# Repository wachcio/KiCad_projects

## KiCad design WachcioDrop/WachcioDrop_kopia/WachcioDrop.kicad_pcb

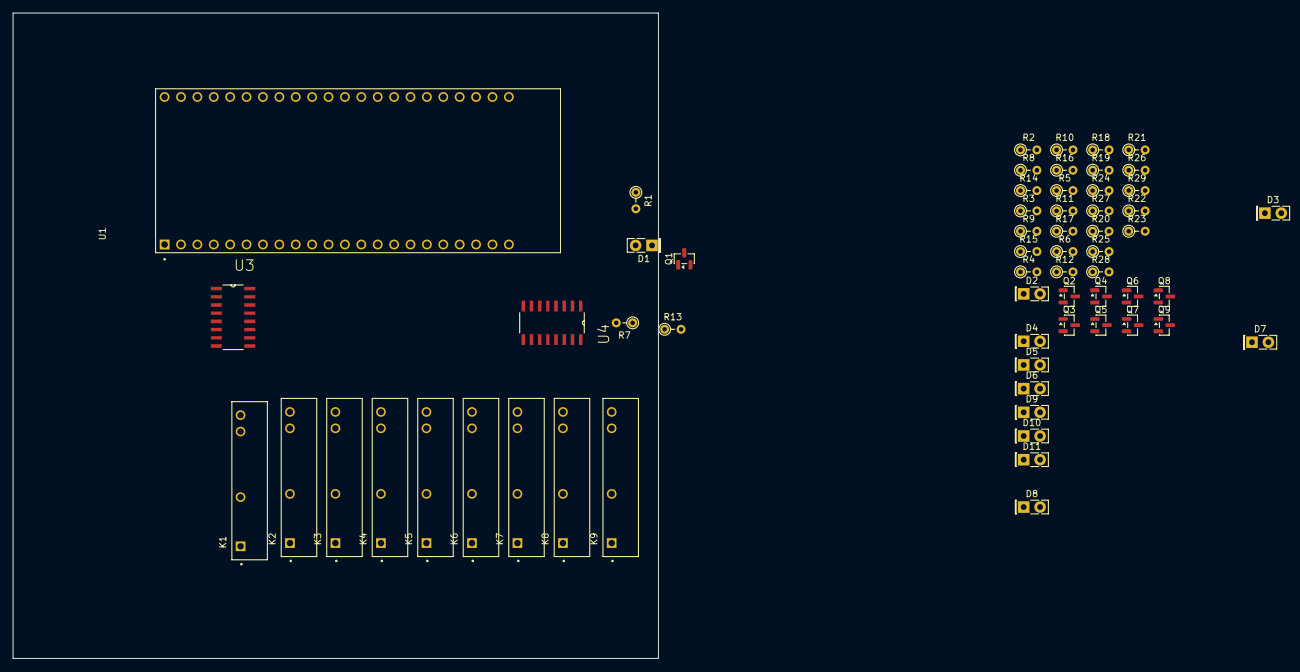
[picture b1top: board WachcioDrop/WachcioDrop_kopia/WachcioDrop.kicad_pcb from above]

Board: 2 copper layers, 100.0 x 100.0 mm, 61 parts (0 on the bottom side), 47 nets, no tracks yet.

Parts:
D1, D2, D3, D4, D5, D6, D8, D9, D10, D11: LED; LED_Rectangular_W5.0mm_H2.0mm
D7: LED niebieski; LED_Rectangular_W5.0mm_H2.0mm
K1, K2, K3, K4, K5, K6, K7, K8, K9: G3MB-202P; RELAY_G3MB-202P
Q1, Q2, Q3, Q4, Q5, Q6, Q7, Q8, Q9: BC847; SOT-23
R1, R2, R3, R4, R5, R6, R19, R20, R21: 270R; R_Axial_DIN0204_L3.6mm_D1.6mm_P2.54mm_Vertical
R7, R8, R9, R10, R11, R12, R24, R25, R26: 4,7K; R_Axial_DIN0204_L3.6mm_D1.6mm_P2.54mm_Vertical
R13, R14, R15, R16, R17, R18, R27, R28, R29: 10K; R_Axial_DIN0204_L3.6mm_D1.6mm_P2.54mm_Vertical
R22, R23: 100R; R_Axial_DIN0204_L3.6mm_D1.6mm_P2.54mm_Vertical
U1: ESP32-S3-DEVKITC-1-N8R2; XCVR_ESP32-S3-DEVKITC-1-N8R2
U3, U4: 74HC595D_118; SOIC127P600X175-16N

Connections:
+3.3V: U1.J1_1 (3V3), U1.J1_2 (3V3), U3.10 (~MR), U3.16 (VCC), U4.10 (~MR), U4.16 (VCC)
+5V: K1.3, K2.3, K3.3, K4.3, K5.3, K6.3, K7.3, K8.3, K9.3, R1.1, R2.1, R3.1, R4.1, R5.1, R6.1, R19.1, R20.1, R21.1, U1.J1_21 (5V0)
/Shift_registers/595_RCLK: U3.12 (ST_CP), U4.12 (ST_CP)
/Shift_registers/595_SRCLK: U3.11 (SH_CP), U4.11 (SH_CP)
/Shift_registers/595_komunikacja: U3.9 (Q7_2), U4.14 (DS)
/Shift_registers/AC_wspolny: K1.2, K2.2, K3.2, K4.2, K5.2, K6.2, K8.2, K9.2
/Shift_registers/power_status: D8.2 (A), U4.2 (Q2)
/Shift_registers/sekcja1: R8.2, U3.1 (Q1)
/Shift_registers/sekcja2: R9.2, U3.2 (Q2)
/Shift_registers/sekcja3: R10.2, U3.3 (Q3)
/Shift_registers/sekcja4: R11.2, U3.4 (Q4)
/Shift_registers/sekcja5: R12.2, U3.5 (Q5)
/Shift_registers/sekcja6: R24.2, U3.6 (Q6)
/Shift_registers/sekcja7: R25.2, U3.7 (Q7)
/Shift_registers/sekcja8: R26.2, U4.15 (Q0)
/Shift_registers/wifi_status: D7.2 (A), U4.1 (Q1)
/Shift_registers/zawor_glowny: R7.2, U3.15 (Q0)
GND: Q1.2 (E), Q2.2 (E), Q3.2 (E), Q4.2 (E), Q5.2 (E), Q6.2 (E), Q7.2 (E), Q8.2 (E), Q9.2 (E), R13.2, R14.2, R15.2, R16.2, R17.2, R18.2, R22.2, R23.2, R27.2, R28.2, R29.2, U1.J1_22 (GND), U1.J3_1 (GND), U1.J3_21 (GND), U1.J3_22 (GND), U3.8 (GND), U3.13 (~OE), U4.8 (GND), U4.13 (~OE)
unnamed: D1.2 (A), R1.2
unnamed: D1.1 (K), K1.4, Q1.3 (C)
unnamed: D2.2 (A), R2.2
unnamed: D2.1 (K), K2.4, Q2.3 (C)
unnamed: D3.2 (A), R3.2
unnamed: D3.1 (K), K3.4, Q3.3 (C)
unnamed: D4.2 (A), R4.2
unnamed: D4.1 (K), K4.4, Q4.3 (C)
unnamed: D5.2 (A), R5.2
unnamed: D5.1 (K), K5.4, Q5.3 (C)
unnamed: D6.2 (A), R6.2
unnamed: D6.1 (K), K6.4, Q6.3 (C)
unnamed: D7.1 (K), R22.1
unnamed: D8.1 (K), R23.1
unnamed: D9.2 (A), R19.2
unnamed: D9.1 (K), K7.4, Q7.3 (C)
unnamed: D10.2 (A), R20.2
unnamed: D10.1 (K), K8.4, Q8.3 (C)
unnamed: D11.2 (A), R21.2
unnamed: D11.1 (K), K9.4, Q9.3 (C)
unnamed: Q1.1 (B), R7.1, R13.1
unnamed: Q2.1 (B), R8.1, R14.1
unnamed: Q3.1 (B), R9.1, R15.1
unnamed: Q4.1 (B), R10.1, R16.1
unnamed: Q5.1 (B), R11.1, R17.1
unnamed: Q6.1 (B), R12.1, R18.1
unnamed: Q7.1 (B), R24.1, R27.1
unnamed: Q8.1 (B), R25.1, R28.1
unnamed: Q9.1 (B), R26.1, R29.1

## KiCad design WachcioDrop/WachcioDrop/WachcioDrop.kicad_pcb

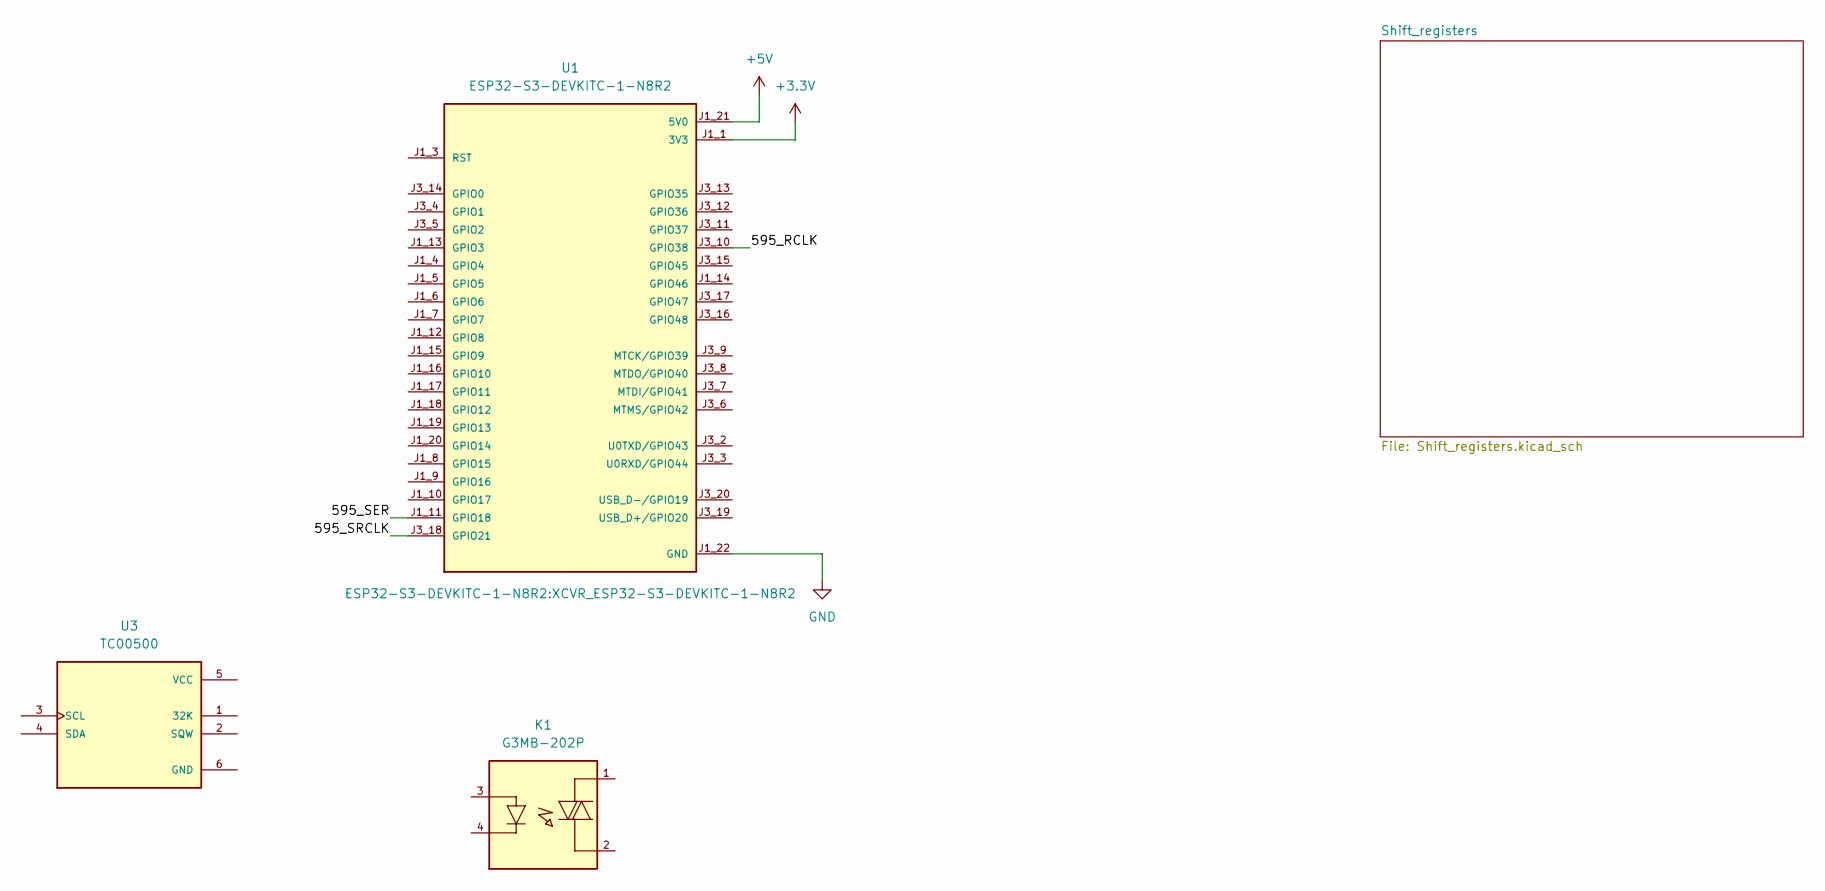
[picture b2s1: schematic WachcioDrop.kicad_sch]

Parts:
K1: G3MB-202P; RELAY_G3MB-202P; PARTREV 06/09
U1: ESP32-S3-DEVKITC-1-N8R2; XCVR_ESP32-S3-DEVKITC-1-N8R2
U3: TC00500; MODULE_TC00500; PARTREV N/A

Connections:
+3.3V: U1.J1_1 (3V3), U1.J1_2 (3V3); also elsewhere on the board
+5V: U1.J1_21 (5V0); also elsewhere on the board
/595_RCLK: U1.J3_10 (GPIO38)
/595_SER: U1.J1_11 (GPIO18)
/595_SRCLK: U1.J3_18 (GPIO21)
GND: U1.J1_22 (GND), U1.J3_1 (GND), U1.J3_21 (GND), U1.J3_22 (GND); also elsewhere on the board

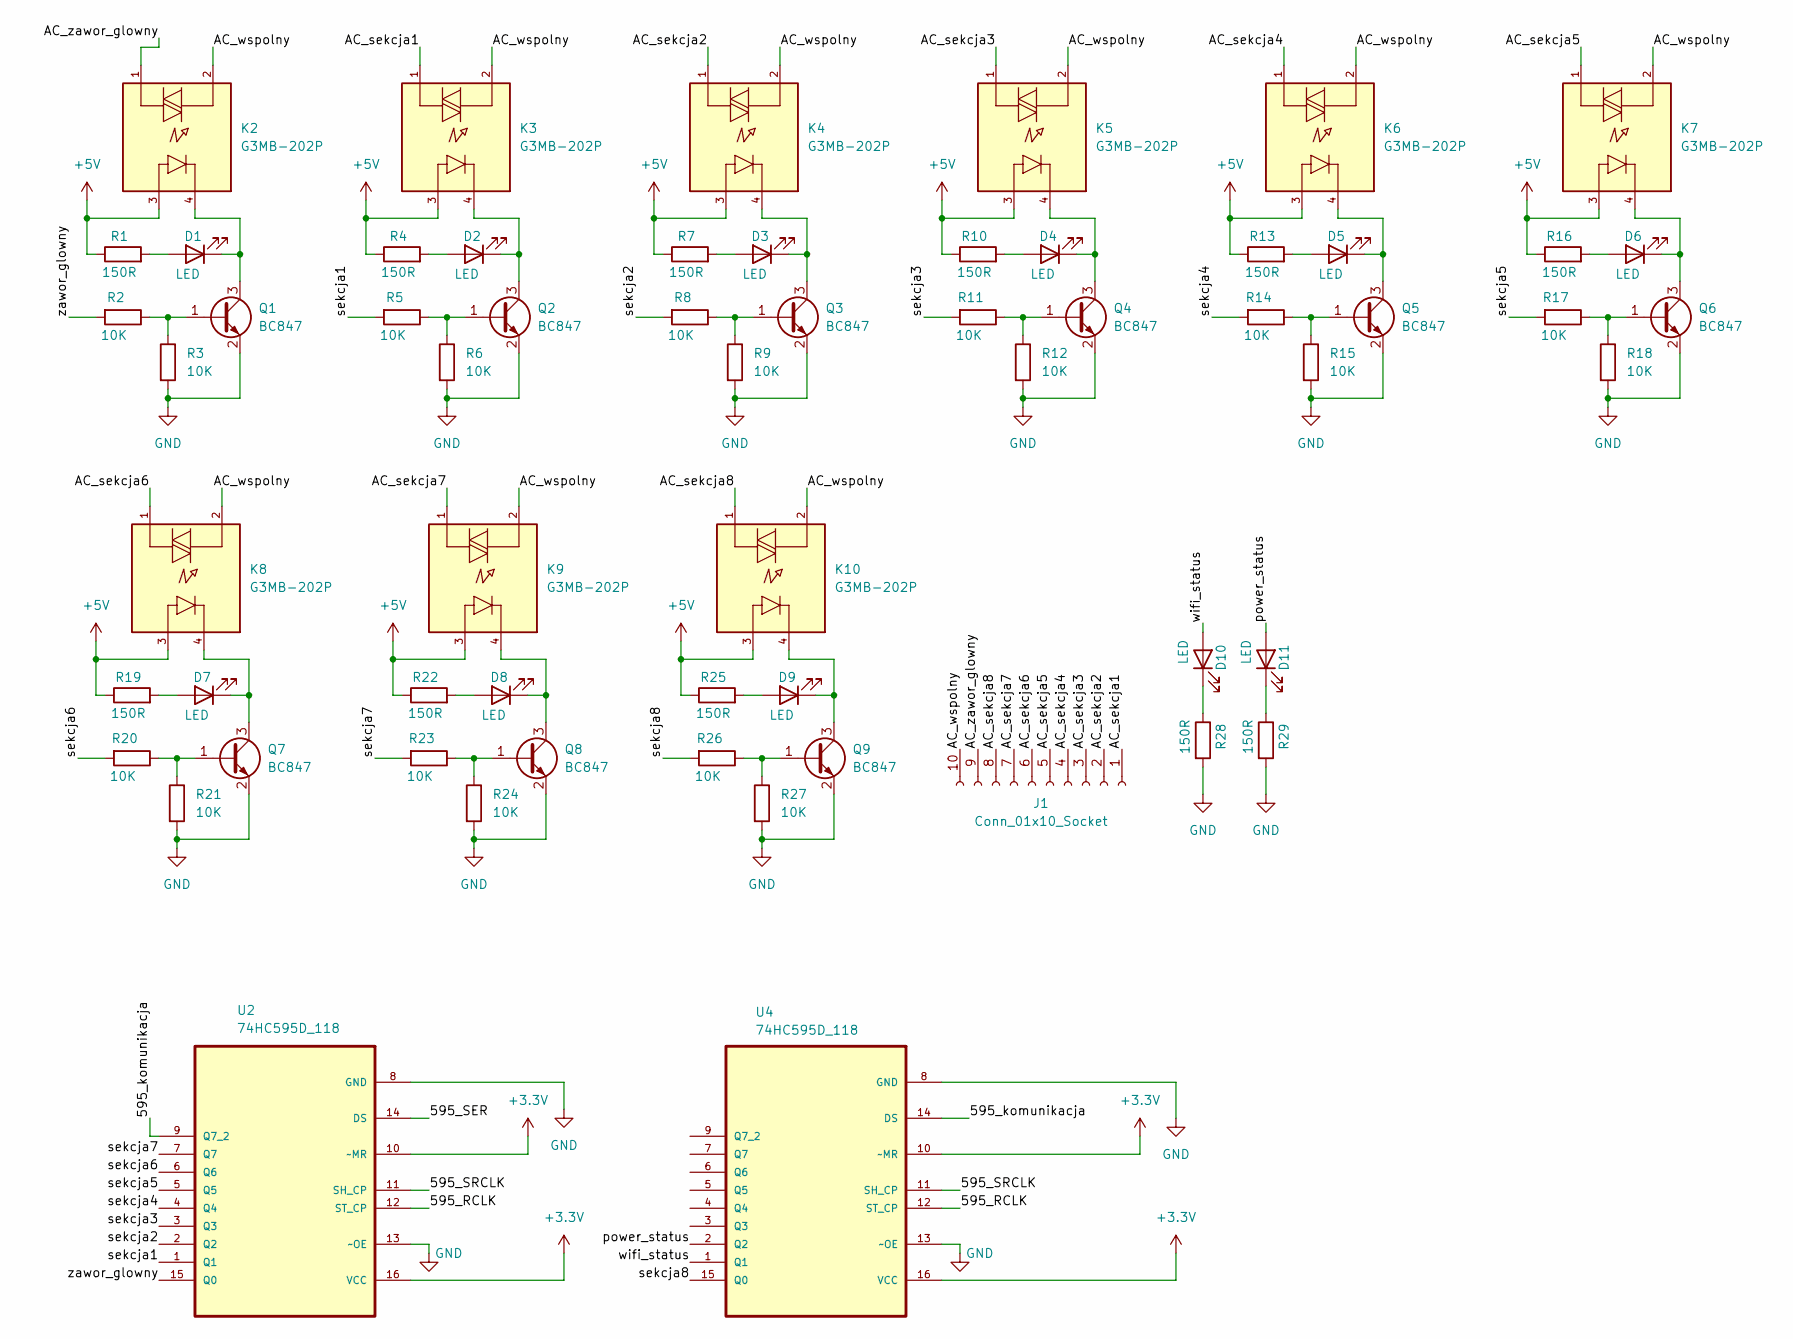
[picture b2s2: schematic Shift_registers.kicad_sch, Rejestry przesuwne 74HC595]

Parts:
D1, D2, D3, D4, D5, D6, D7, D8, D9, D10, D11: LED; LED_Rectangular_W5.0mm_H2.0mm
J1: Conn_01x10_Socket
K2, K3, K4, K5, K6, K7, K8, K9, K10: G3MB-202P; RELAY_G3MB-202P; PARTREV 06/09
Q1, Q2, Q3, Q4, Q5, Q6, Q7, Q8, Q9: BC847; SOT-23
R1, R4, R7, R10, R13, R16, R19, R22, R25, R28, R29: 150R; R_Axial_DIN0204_L3.6mm_D1.6mm_P2.54mm_Vertical
R2, R3, R5, R6, R8, R9, R11, R12, R14, R15, R17, R18, R20, R21, R23, R24, R26, R27: 10K; R_Axial_DIN0204_L3.6mm_D1.6mm_P2.54mm_Vertical
U2, U4: 74HC595D_118; SOIC127P600X175-16N; MPN 74HC595D,118

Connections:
+3.3V: U2.10 (~MR), U2.16 (VCC), U4.10 (~MR), U4.16 (VCC); also elsewhere on the board
+5V: K2.3, K3.3, K4.3, K5.3, K6.3, K7.3, K8.3, K9.3, K10.3, R1.1, R4.1, R7.1, R10.1, R13.1, R16.1, R19.1, R22.1, R25.1; also elsewhere on the board
/Shift_registers/595_RCLK: U2.12 (ST_CP), U4.12 (ST_CP)
/Shift_registers/595_SER: U2.14 (DS)
/Shift_registers/595_SRCLK: U2.11 (SH_CP), U4.11 (SH_CP)
/Shift_registers/595_komunikacja: U2.9 (Q7_2), U4.14 (DS)
/Shift_registers/AC_sekcja1: J1.1, K3.1
/Shift_registers/AC_sekcja2: J1.2, K4.1
/Shift_registers/AC_sekcja3: J1.3, K5.1
/Shift_registers/AC_sekcja4: J1.4, K6.1
/Shift_registers/AC_sekcja5: J1.5, K7.1
/Shift_registers/AC_sekcja6: J1.6, K8.1
/Shift_registers/AC_sekcja7: J1.7, K9.1
/Shift_registers/AC_sekcja8: J1.8, K10.1
/Shift_registers/AC_wspolny: J1.10, K2.2, K3.2, K4.2, K5.2, K6.2, K7.2, K9.2, K10.2
/Shift_registers/AC_zawor_glowny: J1.9, K2.1
/Shift_registers/power_status: D11.2 (A), U4.2 (Q2)
/Shift_registers/sekcja1: R5.2, U2.1 (Q1)
/Shift_registers/sekcja2: R8.2, U2.2 (Q2)
/Shift_registers/sekcja3: R11.2, U2.3 (Q3)
/Shift_registers/sekcja4: R14.2, U2.4 (Q4)
/Shift_registers/sekcja5: R17.2, U2.5 (Q5)
/Shift_registers/sekcja6: R20.2, U2.6 (Q6)
/Shift_registers/sekcja7: R23.2, U2.7 (Q7)
/Shift_registers/sekcja8: R26.2, U4.15 (Q0)
/Shift_registers/wifi_status: D10.2 (A), U4.1 (Q1)
/Shift_registers/zawor_glowny: R2.2, U2.15 (Q0)
GND: Q1.2 (E), Q2.2 (E), Q3.2 (E), Q4.2 (E), Q5.2 (E), Q6.2 (E), Q7.2 (E), Q8.2 (E), Q9.2 (E), R3.2, R6.2, R9.2, R12.2, R15.2, R18.2, R21.2, R24.2, R27.2, R28.2, R29.2, U2.8 (GND), U2.13 (~OE), U4.8 (GND), U4.13 (~OE); also elsewhere on the board
unnamed: D1.2 (A), R1.2
unnamed: D1.1 (K), K2.4, Q1.3 (C)
unnamed: D2.2 (A), R4.2
unnamed: D2.1 (K), K3.4, Q2.3 (C)
unnamed: D3.2 (A), R7.2
unnamed: D3.1 (K), K4.4, Q3.3 (C)
unnamed: D4.2 (A), R10.2
unnamed: D4.1 (K), K5.4, Q4.3 (C)
unnamed: D5.2 (A), R13.2
unnamed: D5.1 (K), K6.4, Q5.3 (C)
unnamed: D6.2 (A), R16.2
unnamed: D6.1 (K), K7.4, Q6.3 (C)
unnamed: D7.2 (A), R19.2
unnamed: D7.1 (K), K8.4, Q7.3 (C)
unnamed: D8.2 (A), R22.2
unnamed: D8.1 (K), K9.4, Q8.3 (C)
unnamed: D9.2 (A), R25.2
unnamed: D9.1 (K), K10.4, Q9.3 (C)
unnamed: D10.1 (K), R28.1
unnamed: D11.1 (K), R29.1
unnamed: Q1.1 (B), R2.1, R3.1
unnamed: Q2.1 (B), R5.1, R6.1
unnamed: Q3.1 (B), R8.1, R9.1
unnamed: Q4.1 (B), R11.1, R12.1
unnamed: Q5.1 (B), R14.1, R15.1
unnamed: Q6.1 (B), R17.1, R18.1
unnamed: Q7.1 (B), R20.1, R21.1
unnamed: Q8.1 (B), R23.1, R24.1
unnamed: Q9.1 (B), R26.1, R27.1

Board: 2 copper layers, 62 parts (0 on the bottom side), 47 nets, no tracks yet.

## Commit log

2026-04-19 19_204_2026
2026-04-19 remove copy
2026-04-20 20_04_2026
2026-04-26 26_04_2026
